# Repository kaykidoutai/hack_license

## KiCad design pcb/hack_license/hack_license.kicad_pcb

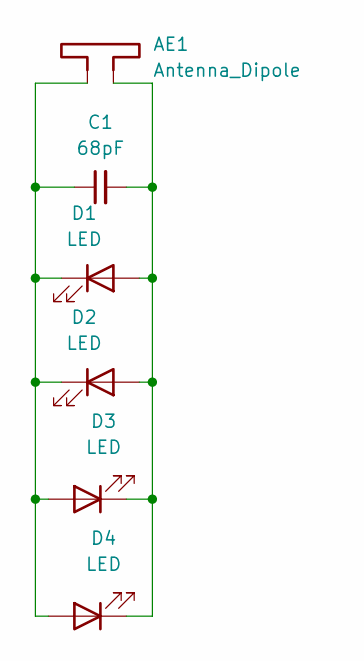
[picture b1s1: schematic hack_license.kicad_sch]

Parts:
AE1: Antenna_Dipole; NFC_ANTENNA
C1: 68pF; C_0603_1608Metric_Pad1.08x0.95mm_HandSolder
D1, D2, D3, D4: LED; LED_0805_2012Metric_Pad1.15x1.40mm_HandSolder

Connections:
unnamed: AE1.1, C1.1, D1.1 (K), D2.1 (K), D3.2 (A), D4.2 (A)
unnamed: AE1.2, C1.2, D1.2 (A), D2.2 (A), D3.1 (K), D4.1 (K)

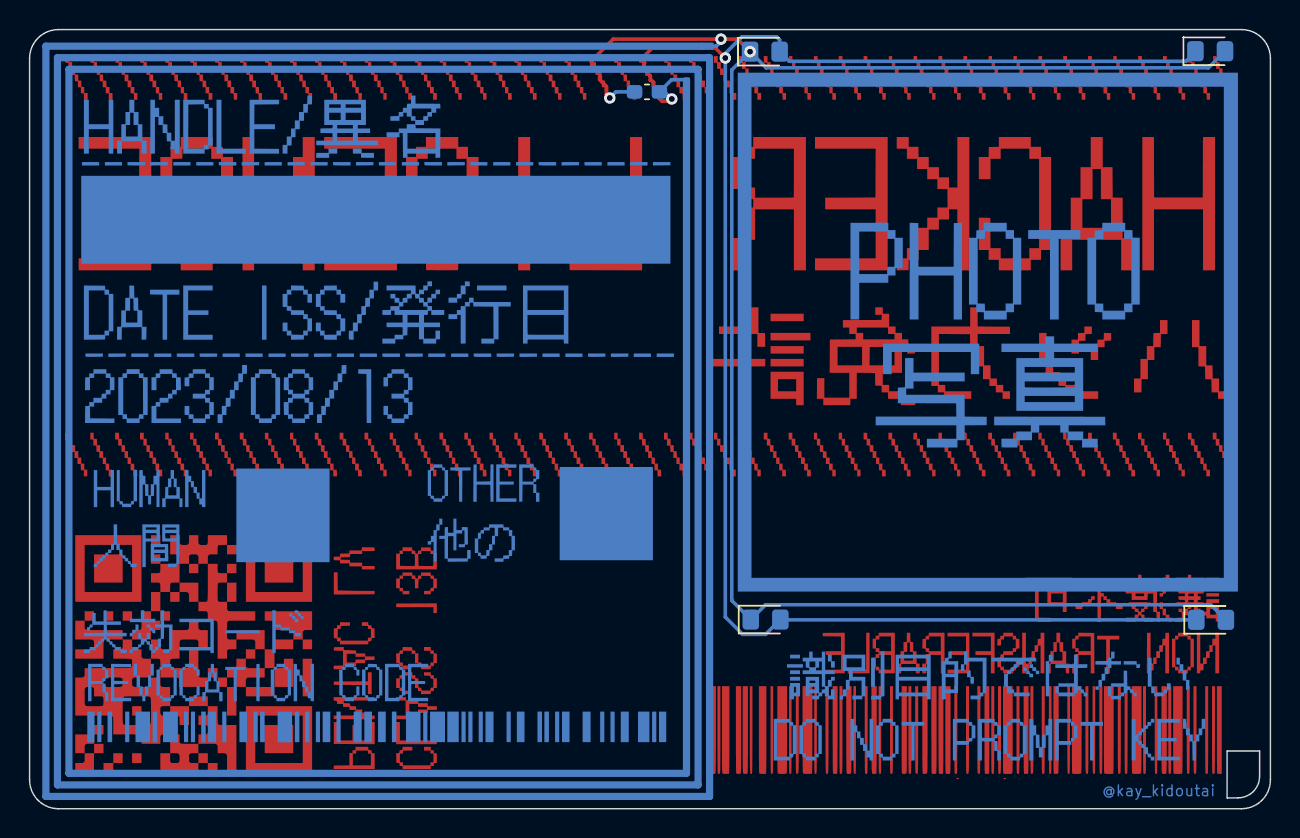
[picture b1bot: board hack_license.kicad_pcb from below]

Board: 2 copper layers, 86.0 x 54.0 mm, 6 parts (6 on the bottom side), 2 nets.

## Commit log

2022-11-08 OOPS
2022-11-24 odered
2023-07-27 stuff
